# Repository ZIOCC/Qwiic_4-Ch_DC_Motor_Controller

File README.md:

# Zio Qwiic 4 DC Motor Controller

> This product can be available for purchase [here](https://www.smart-prototyping.com/Zio-4-DC-Motor-Controller.html).

#### Description

Drive two motors at up to 1.2A of constant current with the Zio Bidirectional 4-Channel DC Motor Controller. Dual H-bridges will allow you to also brake and stop in addition to controlling the direction and speed of the motors. Two input signals (IN1 and IN2) can be used to control the motors with the following functions: CW, CCW, short-brake, and stop. 

You can independently control the two bidirectional DC motors at once. The PWM input allows you to spin the wheels in either direction and at whatever speed you like.

This board also comes equipped with Qwiic connectors so you can quickly and easily daisy-chain to other modules in the Qwiic ecosystem.

> Note: As with all of the Version 1.0 Zio Qwiic boards, this board has been produced with the I2C pull-ups disconnected by default. If there's a significant length of wire between this board and your MCU, you'll need to solder closed the solder jumpers (labeled SDA, 3v3 and SCL) to connect the pull-up resistors to VCC.

#### Specification

* Recommended motor voltage is 2.7 - 5.5V with a max of 15V (For full-current operation at higher voltages, add an appropriate heatsink to prevent triggering the thermal shutdown circuit and to keep the magic smoke inside those precious H-bridges)
* Output current continuous: 1A per channel
* Max. PWM Frequency: 100kHz
* Built-in Power Saving System
* Built-in Thermal Shutdown Circuit and Low Voltage Detecting Circuit
* IC: PCA9685
* I2C address: 0x40-0x7F (default: 0x40)
* Weight: 12.9g (0.45oz)
* Dimension: 54.2x27mm

#### Links

* [PCA9685PW datasheet](https://www.smart-prototyping.com/image/data/NOA-RnD/101897%204%20DC%20Motor%20Driver/PCA9685PW_datasheet.pdf)
* [TB6612FNG datasheet](https://www.smart-prototyping.com/image/data/NOA-RnD/101897%204%20DC%20Motor%20Driver/TB6612FNG_datasheet.pdf)
* [Adafruit PWM Servo Driver Library](https://github.com/adafruit/Adafruit-PWM-Servo-Driver-Library)
* [Demo Code (Solder the pull-up jumpers)](https://www.smart-prototyping.com/image/data/NOA-RnD/101897%204%20DC%20Motor%20Driver/Zio_4_DC_Motor_Controller.ino)
* [Eagle files](https://github.com/ZIOCC/Qwiic_4-Ch_DC_Motor_Controller)

##### Connections for demo

> ###### About Zio
> Zio is a new line of open sourced, compact, and grid layout boards, fully integrated for Arduino and Qwiic ecosystem. Designed ideally for wearables, robotics, small-space limitations or other on the go projects. Check out other awesome Zio products [here](https://www.smart-prototyping.com/Zio).

> All Zio products are released under the [Creative Commons Attribution, Share-Alike License](https://creativecommons.org/licenses/by-sa/4.0/), and in accordance with the principles of the [Open Source Hardware Association's OSHW Statement of Principles 1.0 and OSHW Definition 1.0](https://www.oshwa.org/definition/).

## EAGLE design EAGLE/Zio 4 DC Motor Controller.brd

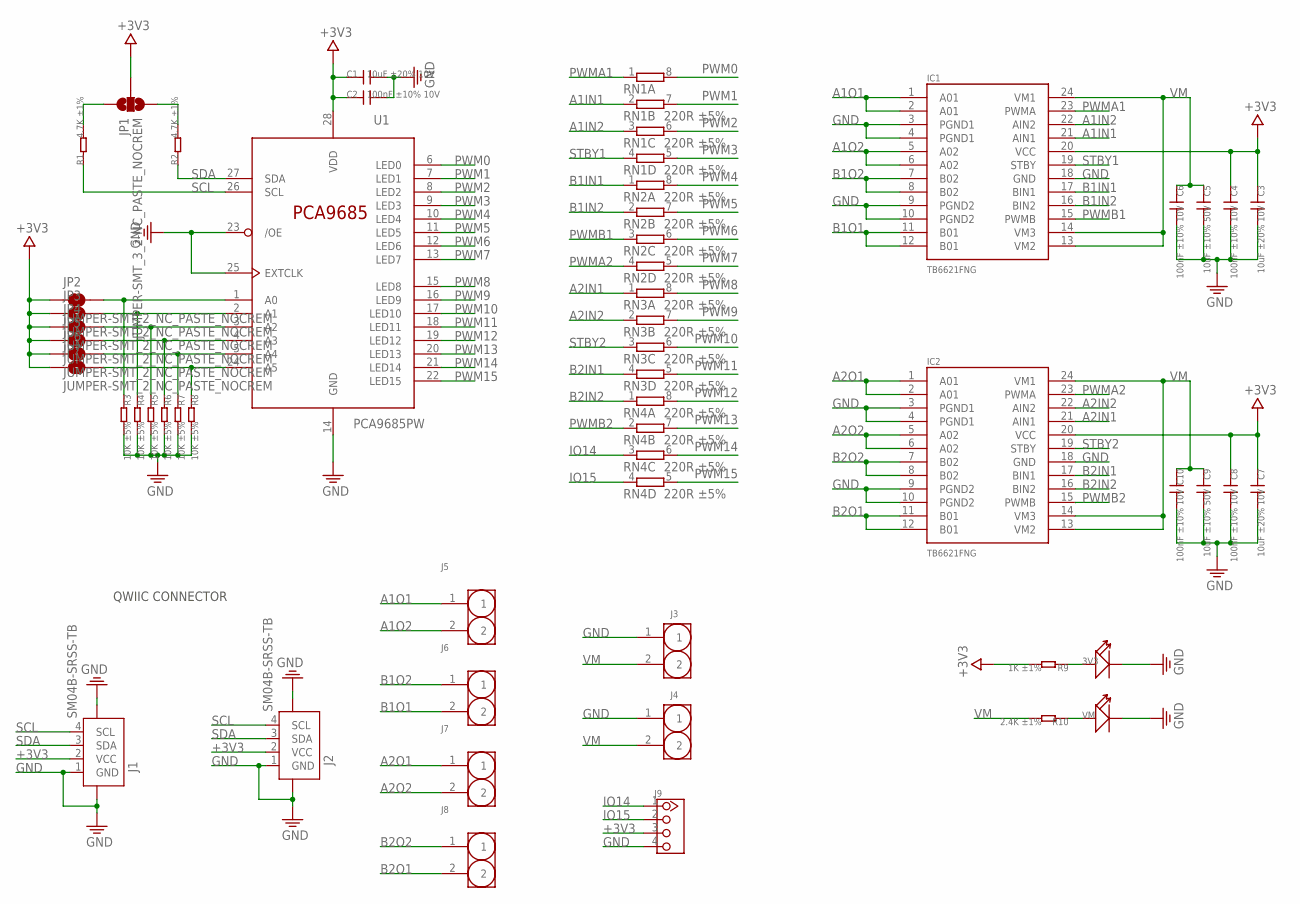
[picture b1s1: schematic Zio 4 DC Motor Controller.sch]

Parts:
3V3: LED'0805'; LED-0805
C1, C3, C7: 10uF ±20% 10V; 0603
C2, C4, C6, C8, C10: 100nF ±10% 10V; 0603
C5, C9: 10uF ±10% 50V; 0805
IC1, IC2: TB6621FNG; SSOP24
J1, J2: SM04B-SRSS-TB; JST-SH-4P
J3, J4: HEADER-2P-2.0-90; PH2.0-2P-90
J5, J6, J7, J8: HEADER-2P-SCREW5.0; 2P-SCREW-5.0
J9: HEADER-4P-80/40MIL; 4P-2.54-80/40MIL
JP1: JUMPER-SMT_3_2-NC_PASTE_NOCREM; SMT-JUMPER_3_2-NC_PASTE_SILK_NOCREM
JP2, JP3, JP4, JP5, JP6, JP7: JUMPER-SMT_2_NC_PASTE_NOCREM; SMT-JUMPER_2_NC_PASTE_SILK_NOCREM
R1, R2: 4.7K ±1%; 0603
R3, R4, R5, R6, R7, R8: 10K ±5%; 0402
R9: 1K ±1%; 0603
R10: 2.4K ±1%; 0603
RN1, RN2, RN3, RN4: 220R ±5%; RESISTOR-DIL_0603-ARV
U1: PCA9685PW; TSSOP28
VM: LED'0805'; LED-0805

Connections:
+3V3: C1.1, C2.1, C3.1, C4.1, C7.1, C8.1, IC1.20 (VCC), IC2.20 (VCC), J1.2 (VCC), J2.2 (VCC), J9.3, JP1.2, JP2.1, JP3.1, JP4.1, JP5.1, JP6.1, JP7.1, R9.2, U1.28 (VDD)
A1IN1: IC1.21 (AIN1), RN1.2 (1)
A1IN2: IC1.22 (AIN2), RN1.3 (1)
A1O1: IC1.1 (A01), IC1.2 (A01), J5.1
A1O2: IC1.5 (A02), IC1.6 (A02), J5.2
A2IN1: IC2.21 (AIN1), RN3.1
A2IN2: IC2.22 (AIN2), RN3.2 (1)
A2O1: IC2.1 (A01), IC2.2 (A01), J7.1
A2O2: IC2.5 (A02), IC2.6 (A02), J7.2
B1IN1: IC1.17 (BIN1), RN2.1
B1IN2: IC1.16 (BIN2), RN2.2 (1)
B1O1: IC1.11 (B01), IC1.12 (B01), J6.2
B1O2: IC1.7 (B02), IC1.8 (B02), J6.1
B2IN1: IC2.17 (BIN1), RN3.4 (1)
B2IN2: IC2.16 (BIN2), RN4.1
B2O1: IC2.11 (B01), IC2.12 (B01), J8.2
B2O2: IC2.7 (B02), IC2.8 (B02), J8.1
GND: 3V3.-, C1.2, C2.2, C3.2, C4.2, C5.2, C6.2, C7.2, C8.2, C9.2, C10.2, IC1.3 (PGND1), IC1.4 (PGND1), IC1.9 (PGND2), IC1.10 (PGND2), IC1.18 (GND), IC2.3 (PGND1), IC2.4 (PGND1), IC2.9 (PGND2), IC2.10 (PGND2), IC2.18 (GND), J1.1 (GND), J1.NC1 (5), J1.NC2 (6), J2.1 (GND), J2.NC1 (5), J2.NC2 (6), J3.1, J4.1, J9.4, R3.2, R4.2, R5.2, R6.2, R7.2, R8.2, U1.14 (GND), U1.23 (/OE), U1.25 (EXTCLK), VM.-
IO14: J9.1, RN4.3 (1)
IO15: J9.2, RN4.4 (1)
unnamed: JP2.2, R3.1, U1.1 (A0)
unnamed: JP3.2, R4.1, U1.2 (A1)
unnamed: JP4.2, R5.1, U1.3 (A2)
unnamed: JP5.2, R6.1, U1.4 (A3)
unnamed: JP6.2, R7.1, U1.5 (A4)
unnamed: JP7.2, R8.1, U1.24 (A5)
unnamed: 3V3.+, R9.1
unnamed: R10.1, VM.+
unnamed: JP1.1, R1.2
unnamed: JP1.3, R2.2
PWM0: RN1.8 (2), U1.6 (LED0)
PWM1: RN1.7 (2), U1.7 (LED1)
PWM2: RN1.6 (2), U1.8 (LED2)
PWM3: RN1.5 (2), U1.9 (LED3)
PWM4: RN2.8 (2), U1.10 (LED4)
PWM5: RN2.7 (2), U1.11 (LED5)
PWM6: RN2.6 (2), U1.12 (LED6)
PWM7: RN2.5 (2), U1.13 (LED7)
PWM8: RN3.8 (2), U1.15 (LED8)
PWM9: RN3.7 (2), U1.16 (LED9)
PWM10: RN3.6 (2), U1.17 (LED10)
PWM11: RN3.5 (2), U1.18 (LED11)
PWM12: RN4.8 (2), U1.19 (LED12)
PWM13: RN4.7 (2), U1.20 (LED13)
PWM14: RN4.6 (2), U1.21 (LED14)
PWM15: RN4.5 (2), U1.22 (LED15)
PWMA1: IC1.23 (PWMA), RN1.1
PWMA2: IC2.23 (PWMA), RN2.4 (1)
PWMB1: IC1.15 (PWMB), RN2.3 (1)
PWMB2: IC2.15 (PWMB), RN4.2 (1)
SCL: J1.4 (SCL), J2.4 (SCL), R1.1, U1.26 (SCL)
SDA: J1.3 (SDA), J2.3 (SDA), R2.1, U1.27 (SDA)
STBY1: IC1.19 (STBY), RN1.4 (1)
STBY2: IC2.19 (STBY), RN3.3 (1)
VM: C5.1, C6.1, C9.1, C10.1, IC1.13 (VM2), IC1.14 (VM3), IC1.24 (VM1), IC2.13 (VM2), IC2.14 (VM3), IC2.24 (VM1), J3.2, J4.2, R10.2

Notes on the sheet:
QWIIC CONNECTOR

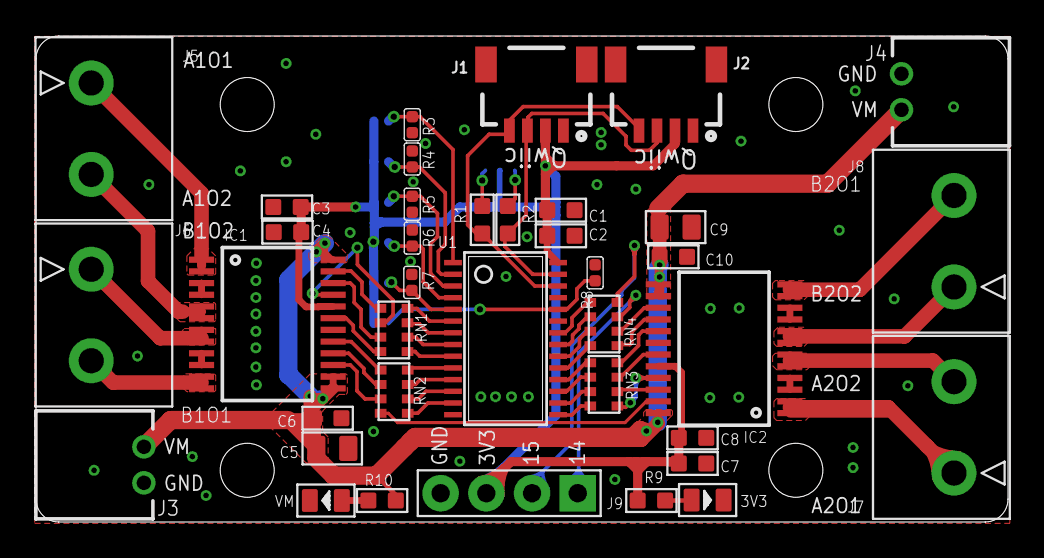
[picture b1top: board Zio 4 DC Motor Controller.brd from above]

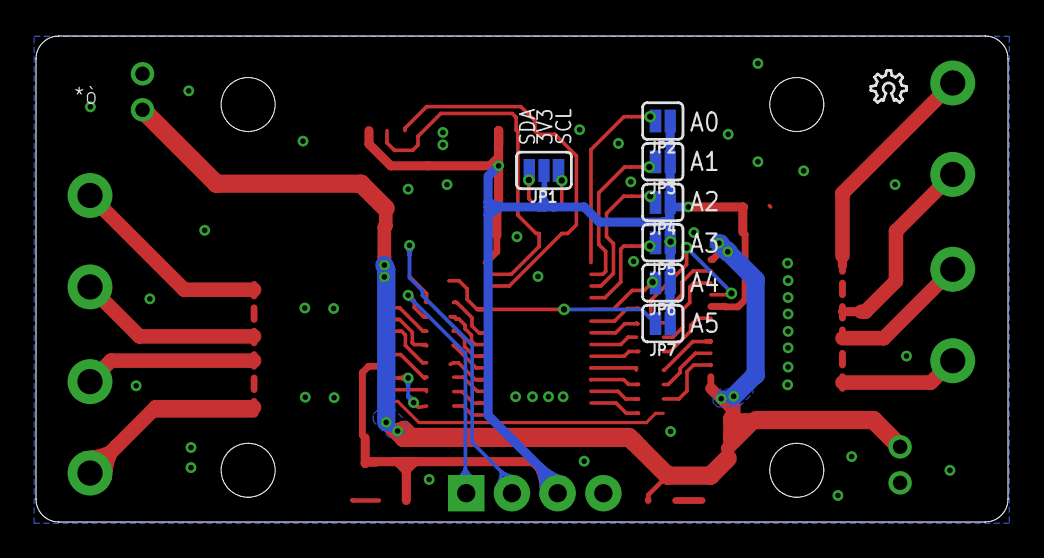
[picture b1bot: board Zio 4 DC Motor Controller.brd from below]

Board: 2 copper layers, 54.0 x 27.0 mm, 48 parts (9 on the bottom side), 55 nets.

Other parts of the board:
E$11: 10MM
LOGO1: LOGO-OSHW-6MILX0070-NT; OSHW_6X70_NOTEXT
U$5: 6MM

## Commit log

2020-06-29 Rename motor.py to qwiic_motor.py
